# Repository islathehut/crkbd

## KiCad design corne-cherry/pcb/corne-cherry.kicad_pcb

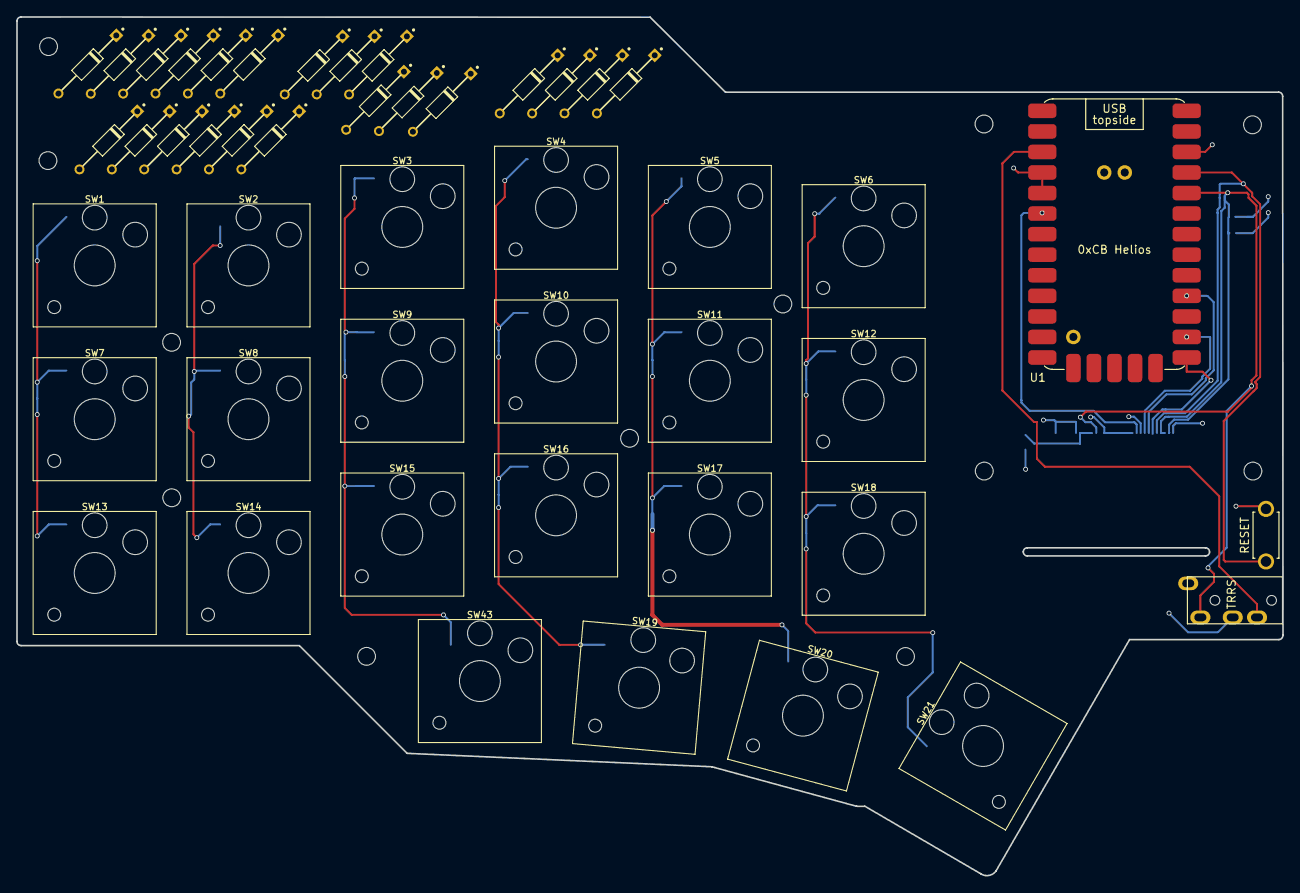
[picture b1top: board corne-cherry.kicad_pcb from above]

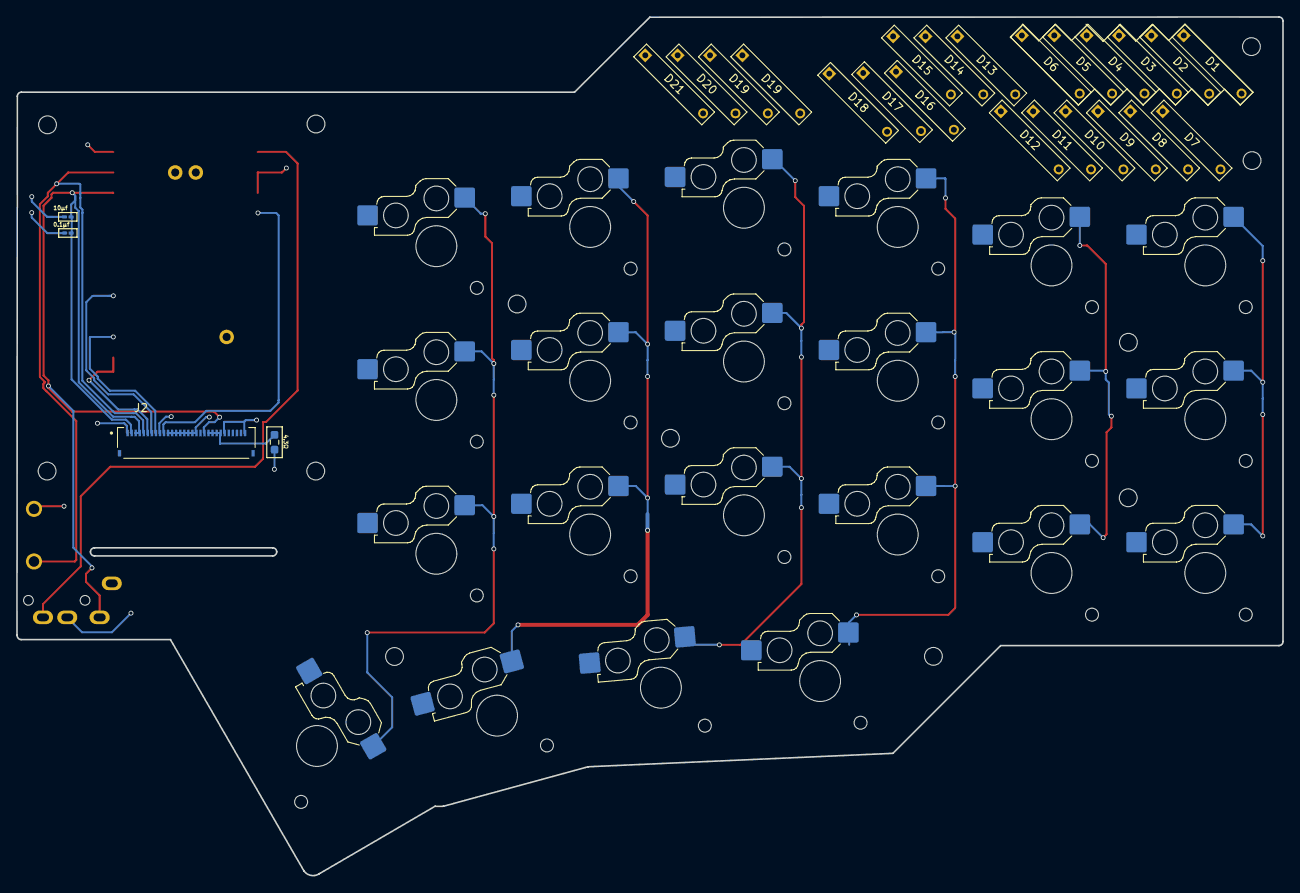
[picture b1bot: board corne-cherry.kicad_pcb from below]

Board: 2 copper layers, 156.4 x 106.1 mm, 63 parts (4 on the bottom side), 15 nets.

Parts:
0.1μf, 10μf: C_Small; R_0201_0603Metric_Pad0.64x0.40mm_HandSolder
4.3Ω: R; R_0603_1608Metric_Pad0.98x0.95mm_HandSolder
D1, D2, D3, D4, D5, D6, D7, D8, D9, D10, D11, D12, D13, D14, D15, D16, D17, D18, D19, D19#2, D20, D21: D; TH 1N4148 Diode (long)
J1: MJ-4PP-9
J2: 30 pin Display Connector; AMPHENOL_F3311A7H121030E200
RSW1: SW_PUSH; ResetSW
Ref**: Val**; MountingHole_2.2mm_M2_DIN965
Ref**#2, Ref**#3, Ref**#4, Ref**#5, Ref**#6, Ref**#7, Ref**#8, Ref**#9, Ref**#10, Ref**#11, Ref**#12: Val**; MountingHole_2.2mm_M2_DIN965
SW1, SW2, SW3, SW4, SW5, SW6, SW7, SW8, SW9, SW10, SW11, SW12, SW13, SW14, SW15, SW16, SW17, SW18, SW19, SW20, SW43: SW_PUSH; SW_Hotswap_Kailh_Choc_V2_1.00u
SW21: SW_PUSH; SW_Hotswap_Kailh_Choc_V2_1.50u
U1: 0xCB Helios; Helios_AC

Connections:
GND: 0.1μf.1, 4.3Ω.1, 10μf.1, J1.C, J2.1 (GND), J2.9 (RD), J2.11 (D0), J2.12 (D1), J2.13 (D3), J2.14 (D4), J2.15 (D5), J2.16 (D6), J2.17 (D7), J2.18 (D8), J2.25 (GND), J2.30 (GND), RSW1.2, U1.3 (GND), U1.4 (GND), U1.14 (GND)
MOSI: J2.8 (SPI-RS), U1.23
unnamed: 4.3Ω.2, J2.21 (LEDK), J2.22 (LEDK), J2.23 (LEDK), J2.24 (LEDK)
SCLK: J2.7 (SCL), U1.21 (P22)
SDA: J2.10 (SDA), U1.5 (P2)
SPI_CS: J2.6 (CS), U1.24 (P21)
VCC: 0.1μf.2, 10μf.2, J1.D, J2.2 (VCC), J2.3 (IM2), J2.4 (IM1), J2.20 (LEDA), U1.16 (3V3)
col0: SW1.1, SW7.1, SW13.1, U1.17 (P29)
col1: SW2.1, SW8.1, SW14.1, U1.18 (P28)
col2: SW3.1, SW9.1, SW15.1, SW43.1, U1.28 (P15)
col3: SW4.1, SW10.1, SW16.1, SW19.1, U1.29 (P16)
col4: SW5.1, SW11.1, SW17.1, SW20.1, U1.11 (P8)
col5: SW6.1, SW12.1, SW18.1, SW21.1, U1.12 (P9)
data: J1.B, U1.2 (P1)
reset: J2.5 (RST), RSW1.1, U1.15 (RST)

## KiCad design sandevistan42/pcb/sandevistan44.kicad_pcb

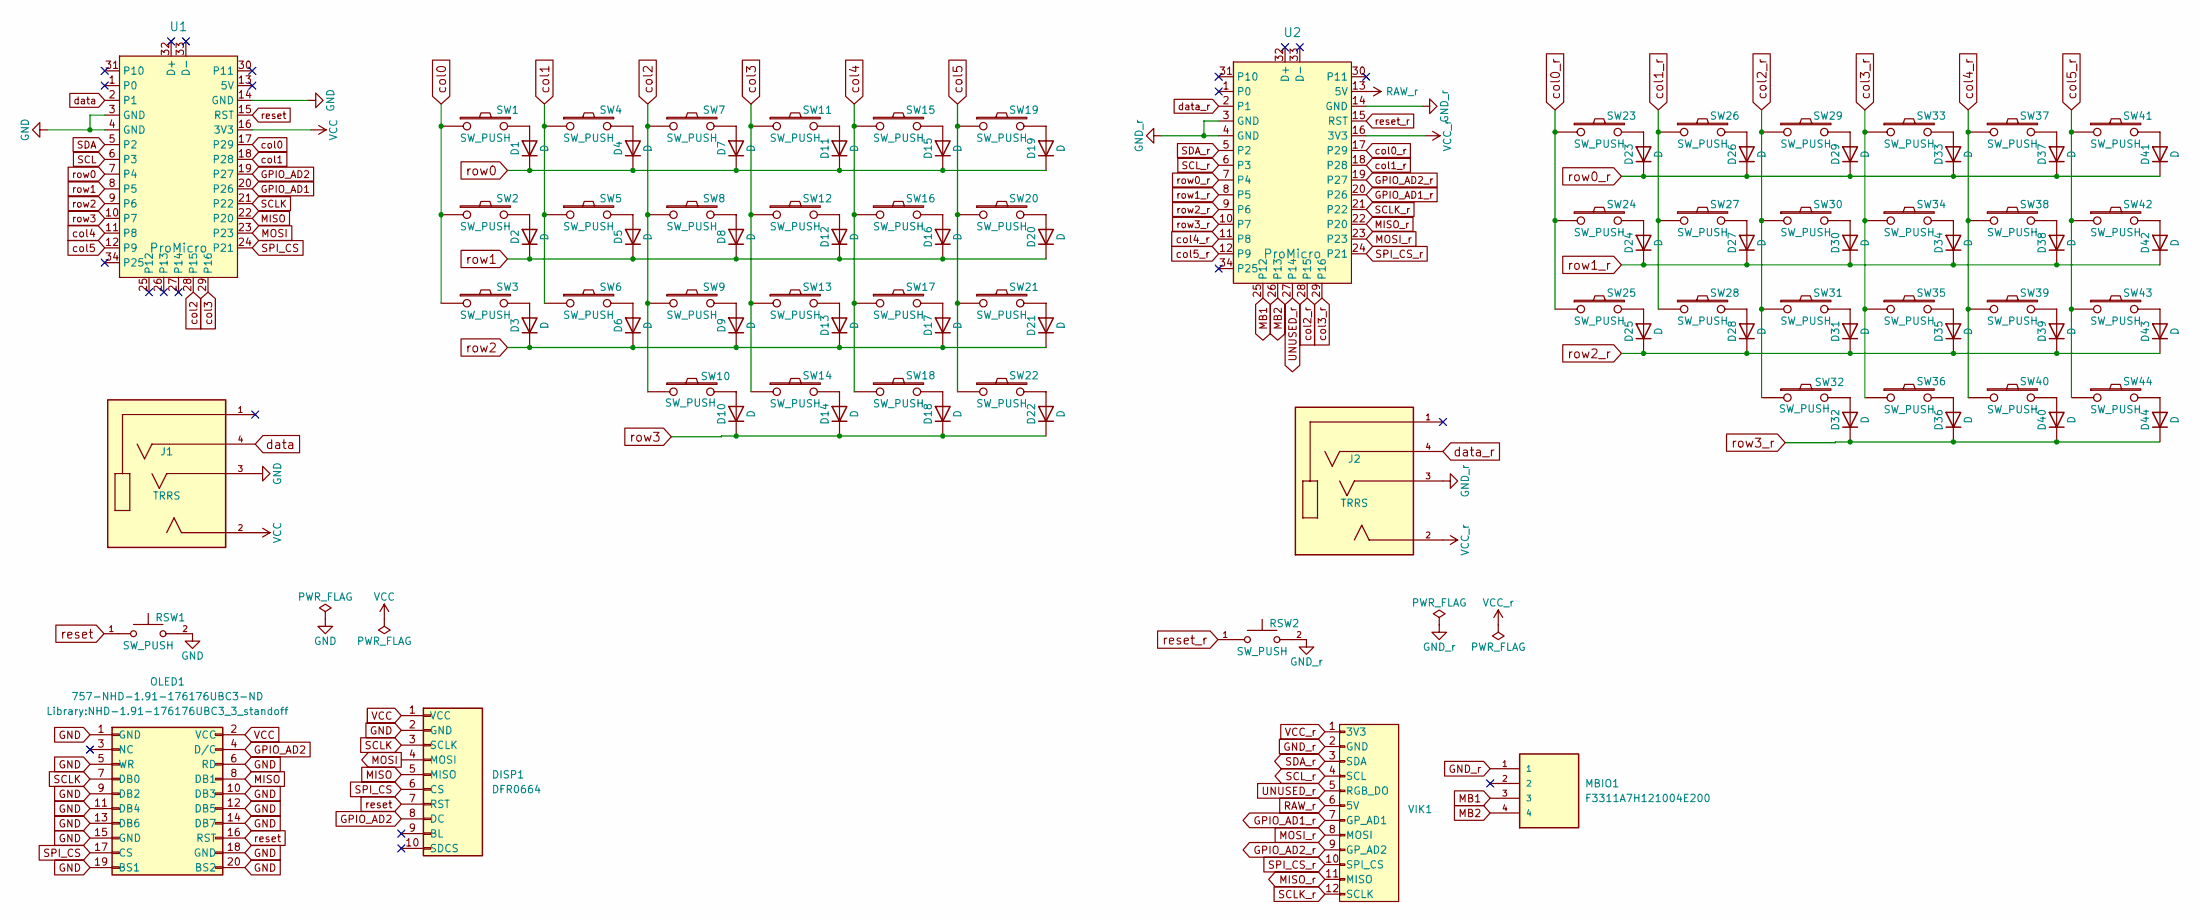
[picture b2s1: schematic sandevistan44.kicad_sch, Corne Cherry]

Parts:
D1, D2, D3, D4, D5, D6, D7, D8, D9, D10, D11, D12, D13, D14, D15, D16, D17, D18, D19, D20, D21, D22, D23, D24, D25, D26, D27, D28, D29, D30, D31, D32, D33, D34, D35, D36, D37, D38, D39, D40, D41, D42, D43, D44: D; TH 1N4148 Diode (long)
DISP1: DFR0664; DFR0664_2in_RGB_TFT_Display
J1, J2: TRRS; CUI_SJ2-35954A-SMT-TR; PARTREV 1.04
MBIO1: F3311A7H121004E200; AMPHENOL_F3311A7H121004E200; PARTREV A
OLED1: 757-NHD-1.91-176176UBC3-ND; NHD-1.91-176176UBC3_3_standoff
RSW1, RSW2: SW_PUSH; SW_TL6340AF160Q; PARTREV 10.23.2019
SW1, SW2, SW3, SW4, SW5, SW6, SW7, SW8, SW9, SW10, SW11, SW12, SW13, SW14, SW15, SW16, SW17, SW18, SW19, SW20, SW21, SW23, SW24, SW25, SW26, SW27, SW28, SW29, SW30, SW31, SW32, SW33, SW34, SW35, SW36, SW37, SW38, SW39, SW40, SW41, SW42, SW43: SW_PUSH; SW_Hotswap_Kailh_Choc_V2_1.00u
SW22, SW44: SW_PUSH; SW_Hotswap_Kailh_Choc_V2_1.25u
U1, U2: ProMicro; Helios_AC
VIK1: vik-keyboard-connector-horizontal-mini

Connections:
GND: DISP1.2 (GND), J1.3, OLED1.1 (GND), OLED1.5 (WR), OLED1.6 (RD), OLED1.9 (DB2), OLED1.10 (DB3), OLED1.11 (DB4), OLED1.12 (DB5), OLED1.13 (DB6), OLED1.14 (DB7), OLED1.15 (GND), OLED1.18 (GND), OLED1.19 (BS1), OLED1.20 (BS2), RSW1.2, U1.3 (GND), U1.4 (GND), U1.14 (GND); also elsewhere on the board
GND_r: J2.3, MBIO1.1, RSW2.2, U2.3 (GND), U2.4 (GND), U2.14 (GND), VIK1.2 (GND); also elsewhere on the board
GPIO_AD1: U1.20 (P26)
GPIO_AD1_r: U2.20 (P26), VIK1.7 (GP_AD1)
GPIO_AD2: DISP1.8 (DC), OLED1.4 (D/C), U1.19 (P27)
GPIO_AD2_r: U2.19 (P27), VIK1.9 (GP_AD2)
MB1: MBIO1.3, U2.25 (P12)
MB2: MBIO1.4, U2.26 (P13)
MISO: DISP1.5 (MISO), OLED1.8 (DB1), U1.22 (P20)
MISO_r: U2.22 (P20), VIK1.11 (MISO)
MOSI: DISP1.4 (MOSI), U1.23
MOSI_r: U2.23, VIK1.8 (MOSI)
unnamed: D1.2 (A), SW1.2
unnamed: D2.2 (A), SW2.2
unnamed: D3.2 (A), SW3.2
unnamed: D4.2 (A), SW4.2
unnamed: D5.2 (A), SW5.2
unnamed: D6.2 (A), SW6.2
unnamed: D7.2 (A), SW7.2
unnamed: D8.2 (A), SW8.2
unnamed: D9.2 (A), SW9.2
unnamed: D10.2 (A), SW10.2
unnamed: D11.2 (A), SW11.2
unnamed: D12.2 (A), SW12.2
unnamed: D13.2 (A), SW13.2
unnamed: D14.2 (A), SW14.2
unnamed: D15.2 (A), SW15.2
unnamed: D16.2 (A), SW16.2
unnamed: D17.2 (A), SW17.2
unnamed: D18.2 (A), SW18.2
unnamed: D19.2 (A), SW19.2
unnamed: D20.2 (A), SW20.2
unnamed: D21.2 (A), SW21.2
unnamed: D22.2 (A), SW22.2
unnamed: D23.2 (A), SW23.2
unnamed: D24.2 (A), SW24.2
unnamed: D25.2 (A), SW25.2
unnamed: D26.2 (A), SW26.2
unnamed: D27.2 (A), SW27.2
unnamed: D28.2 (A), SW28.2
unnamed: D29.2 (A), SW29.2
unnamed: D30.2 (A), SW30.2
unnamed: D31.2 (A), SW31.2
unnamed: D32.2 (A), SW32.2
unnamed: D33.2 (A), SW33.2
unnamed: D34.2 (A), SW34.2
unnamed: D35.2 (A), SW35.2
unnamed: D36.2 (A), SW36.2
unnamed: D37.2 (A), SW37.2
unnamed: D38.2 (A), SW38.2
unnamed: D39.2 (A), SW39.2
unnamed: D40.2 (A), SW40.2
unnamed: D41.2 (A), SW41.2
unnamed: D42.2 (A), SW42.2
unnamed: D43.2 (A), SW43.2
unnamed: D44.2 (A), SW44.2
RAW_r: U2.13 (5V), VIK1.6 (5V)
SCL: U1.6 (P3)
SCLK: DISP1.3 (SCLK), OLED1.7 (DB0), U1.21 (P22)
SCLK_r: U2.21 (P22), VIK1.12 (SCLK)
SCL_r: U2.6 (P3), VIK1.4 (SCL)
SDA: U1.5 (P2)
SDA_r: U2.5 (P2), VIK1.3 (SDA)
SPI_CS: DISP1.6 (CS), OLED1.17 (CS), U1.24 (P21)
SPI_CS_r: U2.24 (P21), VIK1.10 (SPI_CS)
UNUSED_r: U2.27 (P14), VIK1.5 (RGB_DO)
VCC: DISP1.1 (VCC), J1.2, OLED1.2 (VCC), U1.16 (3V3)
VCC_r: J2.2, U2.16 (3V3), VIK1.1 (3V3)
col0: SW1.1, SW2.1, SW3.1, U1.17 (P29)
col0_r: SW23.1, SW24.1, SW25.1, U2.17 (P29)
col1: SW4.1, SW5.1, SW6.1, U1.18 (P28)
col1_r: SW26.1, SW27.1, SW28.1, U2.18 (P28)
col2: SW7.1, SW8.1, SW9.1, SW10.1, U1.28 (P15)
col2_r: SW29.1, SW30.1, SW31.1, SW32.1, U2.28 (P15)
col3: SW11.1, SW12.1, SW13.1, SW14.1, U1.29 (P16)
col3_r: SW33.1, SW34.1, SW35.1, SW36.1, U2.29 (P16)
col4: SW15.1, SW16.1, SW17.1, SW18.1, U1.11 (P8)
col4_r: SW37.1, SW38.1, SW39.1, SW40.1, U2.11 (P8)
col5: SW19.1, SW20.1, SW21.1, SW22.1, U1.12 (P9)
col5_r: SW41.1, SW42.1, SW43.1, SW44.1, U2.12 (P9)
data: J1.4, U1.2 (P1)
data_r: J2.4, U2.2 (P1)
reset: DISP1.7 (RST), OLED1.16 (RST), RSW1.1, U1.15 (RST); also elsewhere on the board
reset_r: RSW2.1, U2.15 (RST); also elsewhere on the board
row0: D1.1 (K), D4.1 (K), D7.1 (K), D11.1 (K), D15.1 (K), D19.1 (K), U1.7 (P4)
row0_r: D23.1 (K), D26.1 (K), D29.1 (K), D33.1 (K), D37.1 (K), D41.1 (K), U2.7 (P4)
row1: D2.1 (K), D5.1 (K), D8.1 (K), D12.1 (K), D16.1 (K), D20.1 (K), U1.8 (P5)
row1_r: D24.1 (K), D27.1 (K), D30.1 (K), D34.1 (K), D38.1 (K), D42.1 (K), U2.8 (P5)
row2: D3.1 (K), D6.1 (K), D9.1 (K), D13.1 (K), D17.1 (K), D21.1 (K), U1.9 (P6)
row2_r: D25.1 (K), D28.1 (K), D31.1 (K), D35.1 (K), D39.1 (K), D43.1 (K), U2.9 (P6)
row3: D10.1 (K), D14.1 (K), D18.1 (K), D22.1 (K), U1.10 (P7)
row3_r: D32.1 (K), D36.1 (K), D40.1 (K), D44.1 (K), U2.10 (P7)

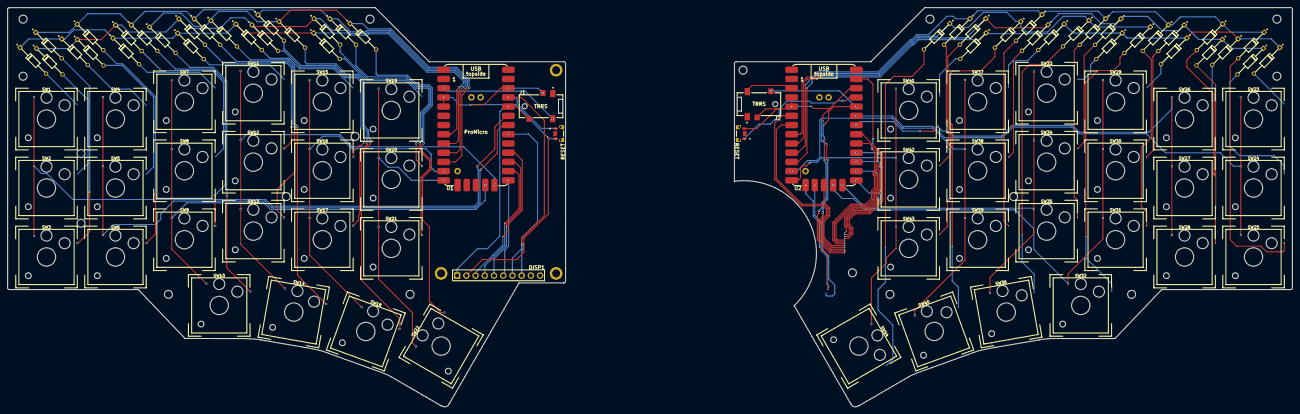
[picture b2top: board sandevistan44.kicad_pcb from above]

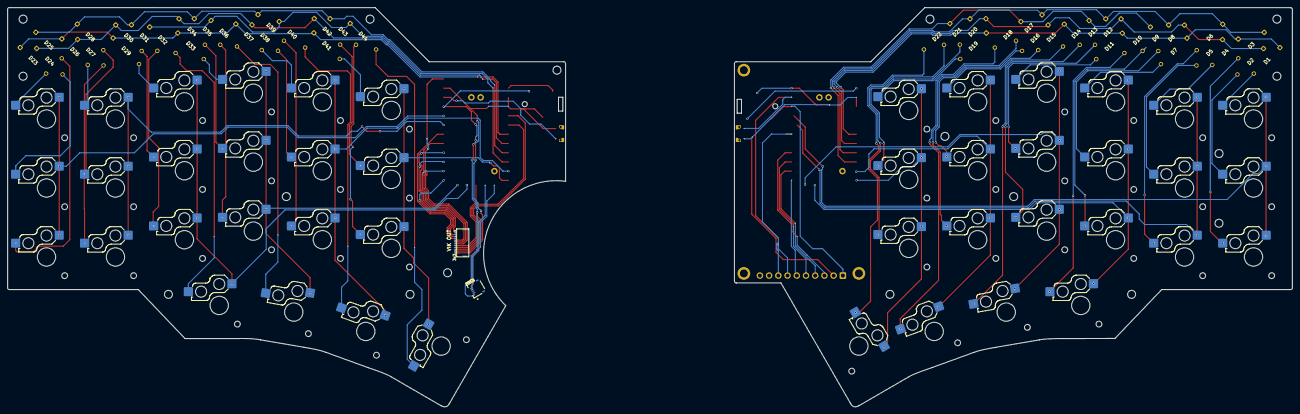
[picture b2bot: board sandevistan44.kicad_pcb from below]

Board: 2 copper layers, 354.0 x 110.0 mm, 114 parts (2 on the bottom side), 89 nets.

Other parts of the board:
RESET: SW_PUSH; SW_TL6340AF160Q
RESET#2: SW_PUSH; SW_TL6340AF160Q
Ref**: Val**; MountingHole_2.2mm_M2_DIN965
Ref**#2, Ref**#3, Ref**#4, Ref**#5, Ref**#6, Ref**#7, Ref**#8, Ref**#10, Ref**#11, Ref**#12, Ref**#13, Ref**#14, Ref**#15, Ref**#16: Val**; MountingHole_2.2mm_M2_DIN965
Ref**#9, Ref**#17: 95.5931; MountingHole_2.2mm_M2_DIN965

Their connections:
GND: RESET.2; also elsewhere on the board
GND_r: RESET#2.2; also elsewhere on the board
reset: RESET.1; also elsewhere on the board
reset_r: RESET#2.1; also elsewhere on the board

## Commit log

2025-05-27 Stashing
2025-05-27 Split pcbs into separate files and add plates
2025-05-27 Remove old and unused files, move to sandevistan44 directory
